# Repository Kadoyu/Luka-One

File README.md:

# 初音ミク Project DIVA MEGA39's+ 用コントローラー「Luka One」  
アーケードLikeなコントローラーです。  
**INFO・CONTACT [https://twitter.com/wakiwakkii](https://twitter.com/wakiwakkii)**　　

2022収穫祭出典品
## Features  
* Divaのアーケードをイメージした配置  
* GP2040を搭載しているため遅延が少ない  
* ★★1677万色に光る★★(理論値)  

## Usage  
ファームウェアは上側面のRESETボタンを２回押すとドライブとして認識されます。  
そこにUF2ファイルをコピペしてください。

Pico Fighting Board用のUF2ファイルを使用してね。
ここからダウンロードできます。
[https://github.com/FeralAI/GP2040/releases](https://github.com/FeralAI/GP2040/releases)

## License
This product is licensed [CC-BY](https://creativecommons.org/licenses/by/4.0/legalcode.txt).

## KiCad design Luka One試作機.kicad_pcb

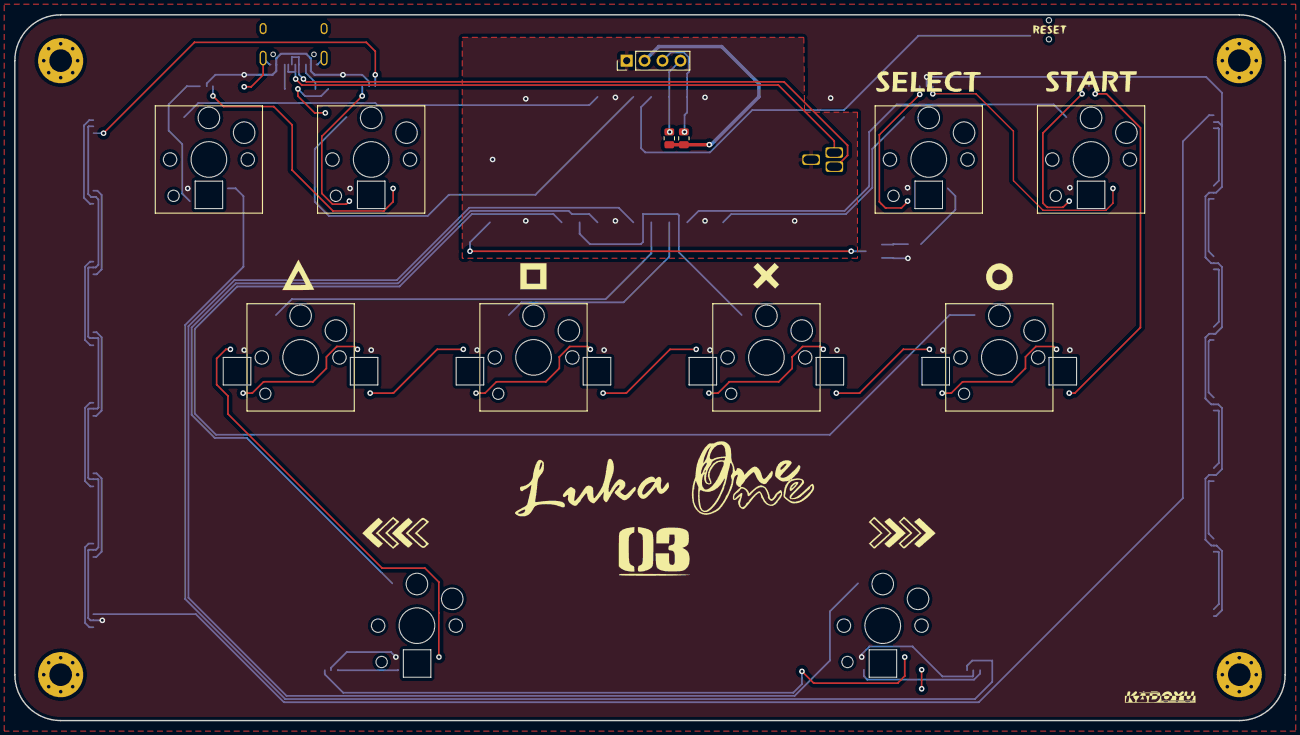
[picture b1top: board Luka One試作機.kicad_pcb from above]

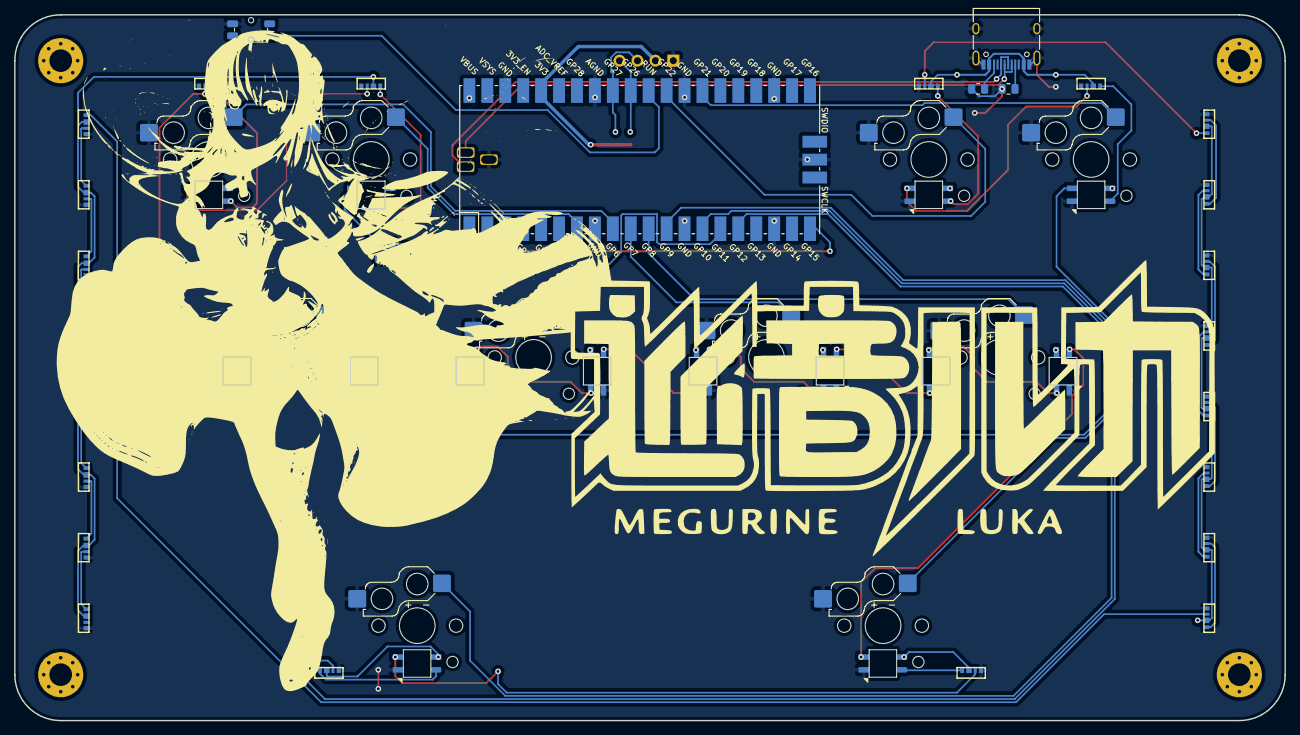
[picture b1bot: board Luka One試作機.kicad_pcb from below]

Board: 2 copper layers, 180.0 x 100.0 mm, 38 parts (29 on the bottom side), 33 nets.

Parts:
C1: 0.1uF; C_0805_2012Metric
J1: USB_C_Receptacle_USB2.0; USB_C_Receptacle_HRO_TYPE-C-31-M-12
J2: Conn_01x04_Male; PinHeader_1x04_P2.54mm_Vertical
Kailh PG1350, Kailh PG1351, Kailh PG1352, Kailh PG1353: Choc; SW_Hotswap_Kailh_Choc_V1V2_1.50u
Kailh PG1354, Kailh PG1354#2: Choc; Kailh-PG1350-2u
LED, LED1, LED2, LED3, LED4, LED5, LED6, LED7, LED8, LED9, LED10, LED11, LED12, LED13, LED14, LED14#2, LED14#3, LED14#4, LED14#5, LED14#6, LED14#7: WS2812B-4020
LED#2: WS2812B-4020
R1, R2: 5.1k; R_0805_2012Metric
R3, R4: 4.7k; R_0805_2012Metric
R5: 330; R_0805_2012Metric
U1: Pico; RPi_Pico_SMD_TH
U2: SN74LV1T34DBV; SOT-23-5

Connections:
/3V3: J2.2, R3.1, R4.1, U1.36 (3V3)
/A: Kailh PG1352.1, U1.15 (GPIO11)
/B: Kailh PG1353.1, U1.16 (GPIO12)
/LB: Kailh PG1354.1, U1.14 (GPIO10)
/RB: Kailh PG1354#2.1, U1.12 (GPIO9)
/RGB: U1.20 (GPIO15), U2.2 (A)
/SCL: J2.3, R3.2, U1.32 (GPIO27_ADC1)
/SDA: J2.4, R4.2, U1.31 (GPIO26_ADC0)
/TP2: J1.A7 (D-), J1.B7 (D-), U1.TP2
/TP3: J1.A6 (D+), J1.B6 (D+), U1.TP3
/X: Kailh PG1351.1, U1.10 (GPIO7)
/Y: Kailh PG1350.1, U1.11 (GPIO8)
GND: C1.1, J1.A1 (GND), J1.A12 (GND), J1.B1 (GND), J1.B12 (GND), J1.S1 (SHIELD), J2.1, Kailh PG1350.2, Kailh PG1351.2, Kailh PG1352.2, Kailh PG1353.2, Kailh PG1354.2, Kailh PG1354#2.2, LED.4, LED1.4, LED2.4, LED3.4, LED4.4, LED5.4, LED6.4, LED7.4, LED8.4, LED9.4, LED10.4, LED11.4, LED12.4, LED13.4, LED14.4, LED14#2.4, LED14#3.4, LED14#4.4, LED14#5.4, LED14#6.4, LED14#7.4, LED#2.4, R1.2, R2.2, U1.3 (GND), U1.8 (GND), U1.13 (GND), U1.18 (GND), U1.23 (GND), U1.28 (GND), U1.33 (AGND), U1.38 (GND), U1.42 (GND), U1.TP1, U2.3 (GND)
unnamed: J1.A5 (CC1), R2.1
unnamed: J1.B5 (CC2), R1.1
unnamed: R5.1, U2.4 (Y)
RGB_DATA_5V_20: LED14#4.3, LED#2.1
RGB_DATA_5V_21: LED1.1, LED#2.3
RGB_DATA_5V_22: LED1.3, LED2.1
RGB_DATA_5V_23: LED2.3, LED3.1
RGB_DATA_5V_24: LED3.3, LED4.1
RGB_DATA_5V_25: LED4.3, LED5.1
RGB_DATA_5V_26: LED5.3, LED6.1
RGB_DATA_5V_27: LED6.3, LED7.1
RGB_DATA_5V_28: LED7.3, LED14#6.1
RGB_DATA_5V_29: LED13.1, LED14#6.3
RGB_DATA_5V_30: LED12.1, LED13.3
RGB_DATA_5V_31: LED11.1, LED12.3
RGB_DATA_5V_32: LED10.1, LED11.3
RGB_DATA_5V_33: LED9.1, LED10.3
RGB_DATA_5V_34: LED8.1, LED9.3
RGB_DATA_5V_35: LED.1, LED8.3
VBUS: C1.2, J1.A4 (VBUS), J1.A9 (VBUS), J1.B4 (VBUS), J1.B9 (VBUS), LED.2, LED1.2, LED2.2, LED3.2, LED4.2, LED5.2, LED6.2, LED7.2, LED8.2, LED9.2, LED10.2, LED11.2, LED12.2, LED13.2, LED14.2, LED14#2.2, LED14#3.2, LED14#4.2, LED14#5.2, LED14#6.2, LED14#7.2, LED#2.2, U1.40 (VBUS), U2.5 (VCC)

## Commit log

2022-10-13 add acrylic case
2022-10-13 Create LICENSE
